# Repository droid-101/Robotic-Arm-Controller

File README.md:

# Robotic Arm Controller

## Background

### Pulse Width Modulation (PWM)

Pule Width Modulation is a a technique of sending variable electrical signals by using digital pulses. By turning a digital output on and off at varying frequencies, an effect can be produced where the signal is recieved at a fraction of the power. For example, a digital signal which is switched between an on state and an off state in equal intervals (50% of the time) will appear to be on at half power. Using this technique of altering the frequencies of these square pulses which are digital signals, variable electrical signals can be created using digital outputs. The servo motors on the robotic arm utilize PWM signals to operate. The PWM wires consist of three different wires carrying 5V+, signal, and GND respectively.

## Robotic Arm

The robotic arm has four different degrees of freedom, each controlled by a small servo motor. These four motors control rotation on the base, extension of the arm, the height of the claws, and the opening and closing of the claws. Each servo motor has a PWM cable over which it can recieve signals from the controller.

## Controller

The controller is a custom made Printed Circuit Board (PCB) which interfaces with the robotic arm's servo motors. It is designed to be plugged into a breadboard and connect to both an external microprocessor, and the robotic arm.

### Power Supply

The controller recieves power through a barrel jack. A 9V adapter is used to plug into a 120V wall socket and supplies the board with power through the barrel jack. Most of the electronic components on the board, as well as the servo motors on the arm, run on 5V. To downstep the voltage, three 7805 voltage regulators are used in parallel to both supply 5V to the circuit, and to prevent the board from overheating from high current draw.

### Controls

The controller has four potentiometers and one button as a part of its control set. Each potentiometer is isolated on its own channel on which it can be sampled for its current value by an external microprocessor. This allows for each joint on the robotic arm to have its own separate control. The button on the circuit board can also be read for its current state. It can serve as a trigger, or as a reset button.

### Reading and Writing

The controller has multiple sets of sip pins which connect to different components. The row of five sip pins connect to the button and potentionmeters and serve as inputs for the microprocessor to sample. The row of four sip pins are output pins which the microprocessor can use to write PWM signals to the servo motors. Each pin corresponds to a specific servo motor on the arm. The last set of four rows of three sip pins are connectors for the servo motors and allow for each motor to recieve power, and its respective signal from the microprocessor.

### Schematic

### Trace Mask

### Controller Circuit Board

## Arduino

The controller board was connected to an Arduino to manage reading the controls and writing angle values to the arm's servo motors. 

### Pinouts

The Arduino is capable of reading inputted analog signals which are inputted on the analog pins. Each potentiometer on the controller board is connected to one analog pin. The programme running on the Arduino will read the analog value on the pin and use it to write an angle to the servo motor. The Arduino has multiple digital pinouts which support PWM communication. These pins were used to send PWM signals to the servo motors. They output directly onto the signal lines feeding into the servo motors. Each pinout attaches to only one signal line and controls only one motor. The button on the controller board is also attached to one digital pin so that its state can be sampled.

### Keyboard Control

In addition to being controlled via the potentiometers on the circuit board, the robotic arm can also be controlled by a computer keyboard. Once the Arduino is connected to a computer using a USB cable, keyboard inputs are sent to the Arduino over Serial communication. The programme then determines which changes must be made to which motors depending on which key was pressed.

## Revisions

 After the PCB for the controller was created, a short circuit was found to exist in the printed traces. This was manually corrected on the underside of the board. Upon using the controller with the Arduino and the robotic arm, the servo motors were found to perform in a choppy fashion. This was solved by connecting the Arduino, the controller, and the servo motors to a common ground.

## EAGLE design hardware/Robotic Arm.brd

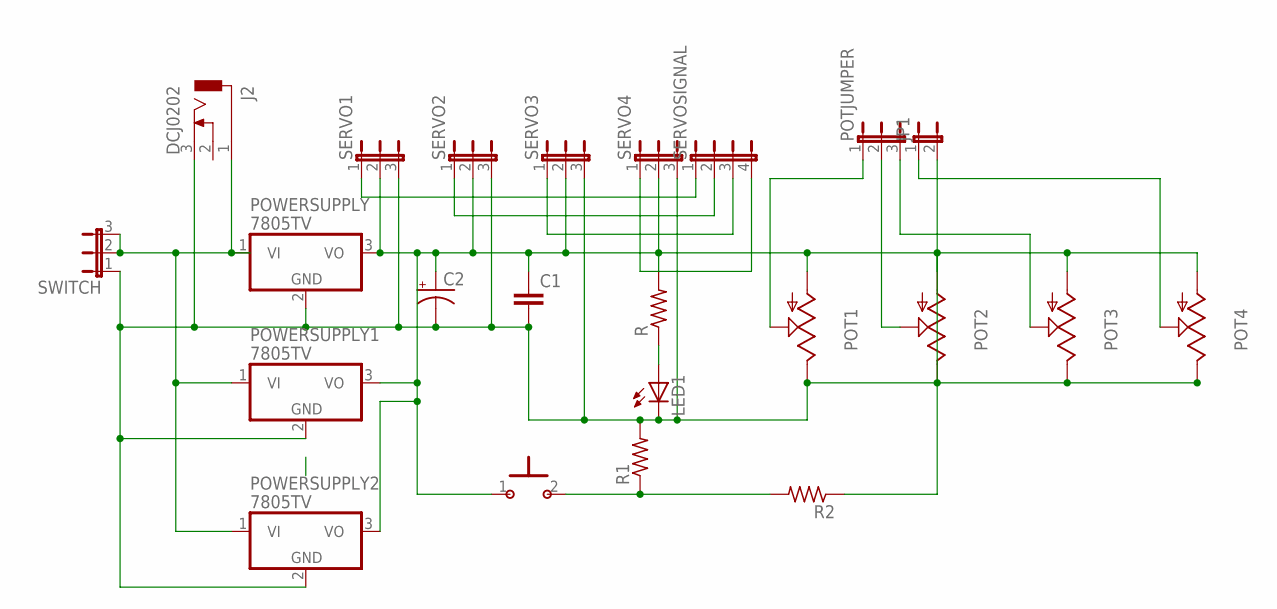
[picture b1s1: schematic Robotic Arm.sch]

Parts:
C1: C-EU050-025X075; C050-025X075
C2: CPOL-USE3.5-8; E3,5-8
J2: DCJ0202
JP1: JP1E; JP1
LED1: LED5MM
POT1, POT2, POT3, POT4: TRIM_US-B25P; B25P
POTJUMPER: JP2E; JP2
POWERSUPPLY, POWERSUPPLY1, POWERSUPPLY2: 7805TV; TO220V
R, R1, R2: R-US_0207/10; 0207/10
SERVO1, SERVO2, SERVO3, SERVO4: JP2E; JP2
SERVOSIGNAL: JP4E; JP4
SWITCH: JP2E; JP2
U$1: PUSHBUTTON

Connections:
unnamed: C1.2, C2.-, J2.3, LED1.K (C), POT1.E, POT2.E, POT3.E, POT4.E, POWERSUPPLY.2 (GND), POWERSUPPLY1.2 (GND), POWERSUPPLY2.2 (GND), R1.2, SERVO1.3, SERVO2.3, SERVO3.3, SERVO4.3, SWITCH.1
unnamed: C1.1, C2.+, POT1.A, POT2.A, POT3.A, POT4.A, POWERSUPPLY.3 (VO), POWERSUPPLY1.3 (VO), POWERSUPPLY2.3 (VO), R.2, SERVO1.2, SERVO2.2, SERVO3.2, SERVO4.2, U$1.1
unnamed: LED1.A, R.1
unnamed: J2.1, POWERSUPPLY.1 (VI), POWERSUPPLY1.1 (VI), POWERSUPPLY2.1 (VI), SWITCH.2, SWITCH.3
unnamed: POT1.S, POTJUMPER.1
unnamed: POT2.S, POTJUMPER.2
unnamed: JP1.1, POT4.S
unnamed: SERVO1.1, SERVOSIGNAL.1
unnamed: SERVO2.1, SERVOSIGNAL.2
unnamed: SERVO3.1, SERVOSIGNAL.3
unnamed: SERVO4.1, SERVOSIGNAL.4
unnamed: POT3.S, POTJUMPER.3
unnamed: R1.1, R2.2, U$1.2
unnamed: JP1.2, R2.1

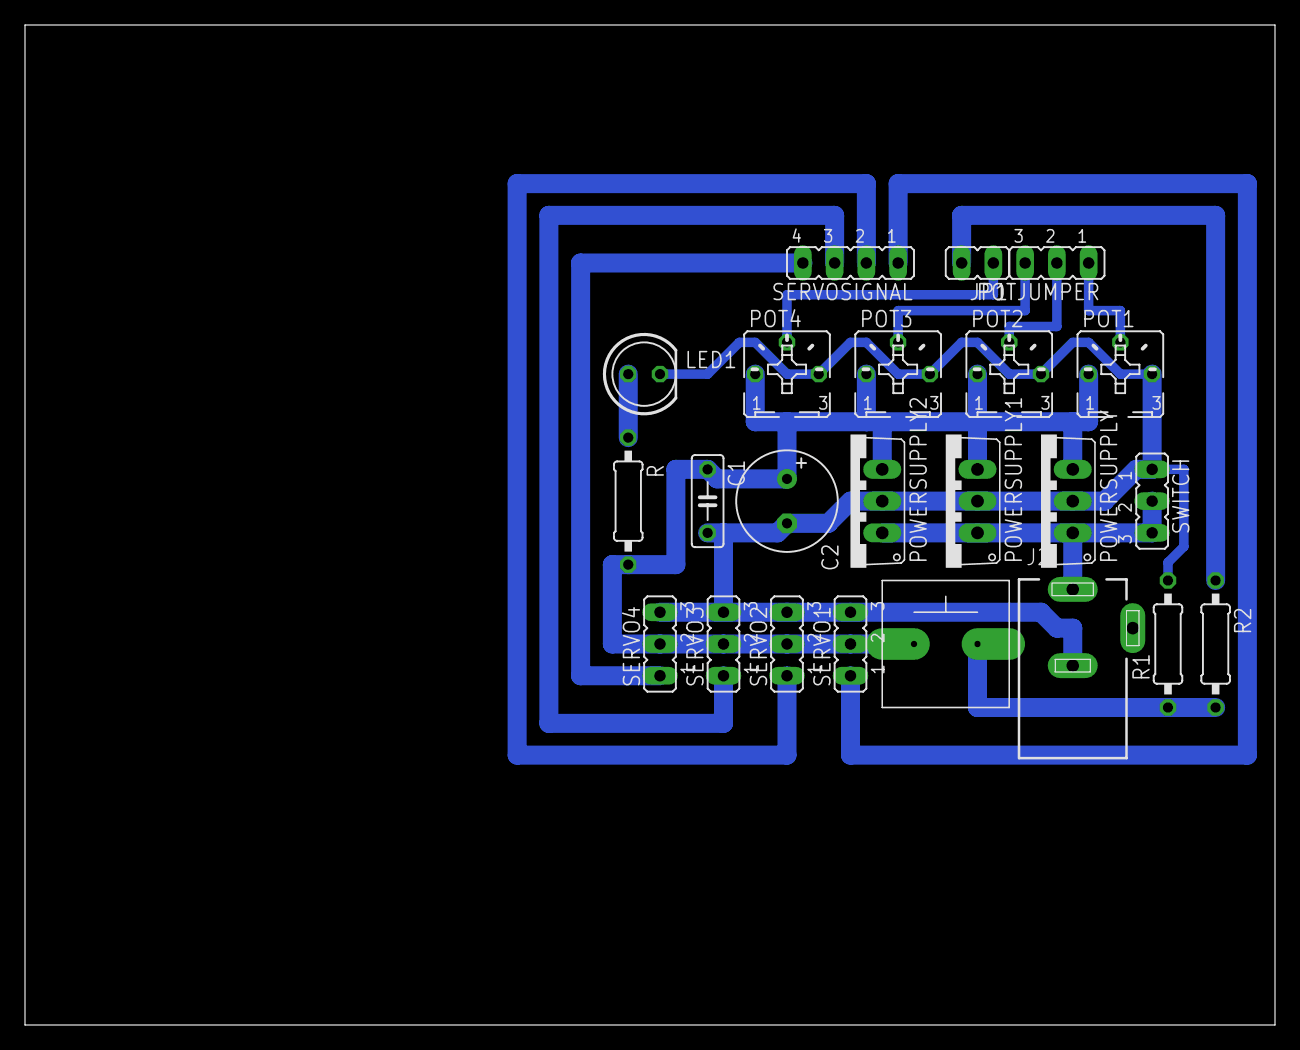
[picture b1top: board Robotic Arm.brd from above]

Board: 2 copper layers, 100.0 x 80.0 mm, 23 parts (0 on the bottom side), 14 nets.

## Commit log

2023-01-10 Updated Readme File
